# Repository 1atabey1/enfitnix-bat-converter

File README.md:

# ENFITNIX Battery Converter

**NOTE: The current release (1.0.0) is not functional without workarounds. See [issues](https://github.com/1atabey1/enfitnix-bat-converter/issues) for more info.**

Bike lights by Enfitnix use the quite common 18650 form factor for their batteries. However, they require a very specific protection PCB that exposes both poles of the battery in two concentric circles on one side.

It's kinda hard to get these batteries (at least in Europe -> over 30€ for a single [battery](https://de.grandado.com/products/enfitnix-navi800-fahrrad-licht-lg-3350mah-akku-integrierte-hohe-prazision-batterie)!!!), so this custom PCB offers the option of converting almost any 18650 battery into one that fits your bike light for a BOM cost of just around 1€.

## Order

Any non-basic part has an LCSC part number attached so you can directly upload the files from the latest [release](https://github.com/1atabey1/enfitnix-bat-converter/releases) to JLCPCB and order the fully assembled PCBs.

## Limitations

The current design is parametrised as follows

```
OVP: 4.2V
UVP: 2.5V
OCC: 18A
OCD: 40A
```

Before use, please confirm your cell's voltage range aligns with these limits (i.e. max cell operating voltage > OVP and min cell operating voltage < UVP). 

This will **not** work for LFP based cells!

## Usage

I recommend using heat shrink and a plastic base for the PCB as you get it from e.g. [AliExpress](https://de.aliexpress.com/item/32855964562.html)

With that the process is quite simple:
1. Solder one nickel strip each to the pads marked with + and -
2. Thread nickel strips through plastic base
3. Spot weld respective strips to their corresponding terminal of the cell
4. Wrap it all up in heat shrink

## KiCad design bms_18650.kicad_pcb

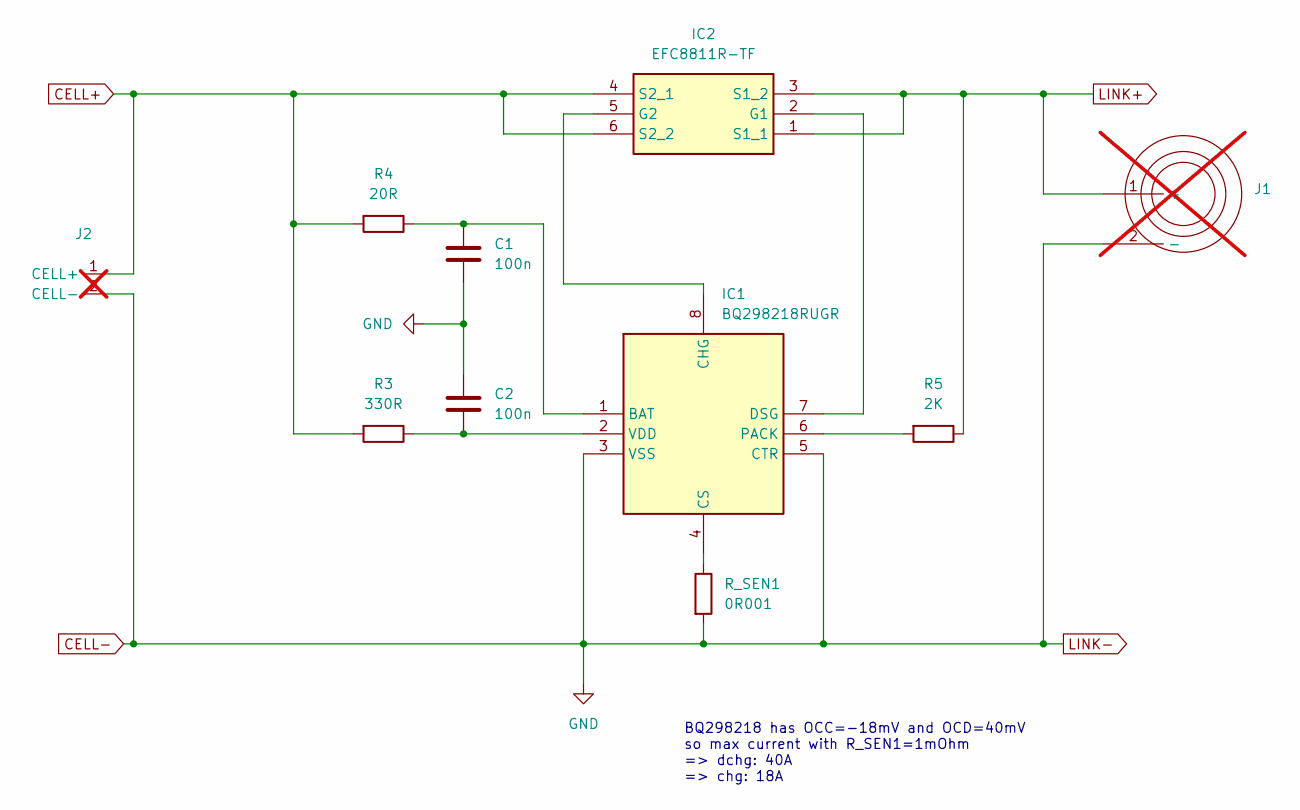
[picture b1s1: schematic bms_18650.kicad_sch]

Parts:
C1, C2: 100n; C_0805_2012Metric_Pad1.18x1.45mm_HandSolder
IC1: BQ298218RUGR; ADS7056IRUGR; Manufacturer_Part_Number BQ298000RUGR; Mouser Part Number 595-BQ298000RUGR
IC2: EFC8811R-TF; EFC8811RTF; Manufacturer_Part_Number EFC8811R-TF; Mouser Part Number 863-EFC8811R-TF
J1: ENFITNIX_BAT; not fitted
J2: CELL_LEAD_CONN; not fitted
R3: 330R; R_0805_2012Metric_Pad1.20x1.40mm_HandSolder
R4: 20R; R_0805_2012Metric_Pad1.20x1.40mm_HandSolder
R5: 2K; R_0805_2012Metric_Pad1.20x1.40mm_HandSolder
R_SEN1: 0R001; R_0805_2012Metric_Pad1.20x1.40mm_HandSolder; LCSC C4337252

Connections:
CELL+: IC2.4 (S2_1), IC2.6 (S2_2), J2.1 (CELL+), R3.2, R4.2
CELL-: C1.2, C2.1, IC1.3 (VSS), IC1.5 (CTR), J1.2 (-), J2.2 (CELL-), R_SEN1.2
LINK+: IC2.1 (S1_1), IC2.3 (S1_2), J1.1 (+), R5.1
unnamed: C1.1, IC1.1 (BAT), R4.1
unnamed: IC1.8 (CHG), IC2.5 (G2)
unnamed: IC1.4 (CS), R_SEN1.1
unnamed: IC1.7 (DSG), IC2.2 (G1)
unnamed: IC1.6 (PACK), R5.2
unnamed: C2.2, IC1.2 (VDD), R3.1

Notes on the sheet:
BQ298218 has OCC=-18mV and OCD=40mV so max current with R_SEN1=1mOhm => dchg: 40A => chg: 18A

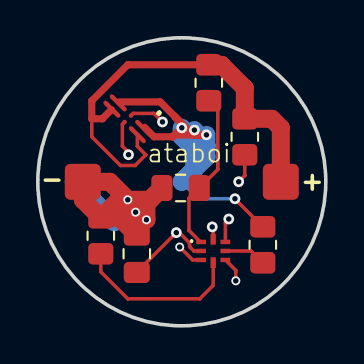
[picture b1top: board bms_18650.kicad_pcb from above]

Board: 4 copper layers, 16.0 x 16.0 mm, 10 parts (0 on the bottom side), 9 nets.

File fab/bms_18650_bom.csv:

"Designator","Comment","Footprint","LCSC"
"C1,C2","100n","Capacitor_SMD:C_0805_2012Metric_Pad1.18x1.45mm_HandSolder",""
"IC1","BQ298218RUGR","ADS7056IRUGR","C36857140"
"IC2","EFC8811R-TF","EFC8811RTF","C895369"
"R3","330R","Resistor_SMD:R_0805_2012Metric_Pad1.20x1.40mm_HandSolder",""
"R4","20R","Resistor_SMD:R_0805_2012Metric_Pad1.20x1.40mm_HandSolder",""
"R5","2K","Resistor_SMD:R_0805_2012Metric_Pad1.20x1.40mm_HandSolder",""
"R_SEN1","0R001","Resistor_SMD:R_0805_2012Metric_Pad1.20x1.40mm_HandSolder","C4337252"

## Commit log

2025-10-20 add initial files
2025-10-30 first ordered revision
2025-10-30 add readme
2025-10-30 udpate readme
2025-10-31 no more blind vias
2025-12-31 Update README with release note for version 1.0.0
    Added a note about the current release not being functional without workarounds.
2026-01-06 fix footprint
    fixes issue #1
